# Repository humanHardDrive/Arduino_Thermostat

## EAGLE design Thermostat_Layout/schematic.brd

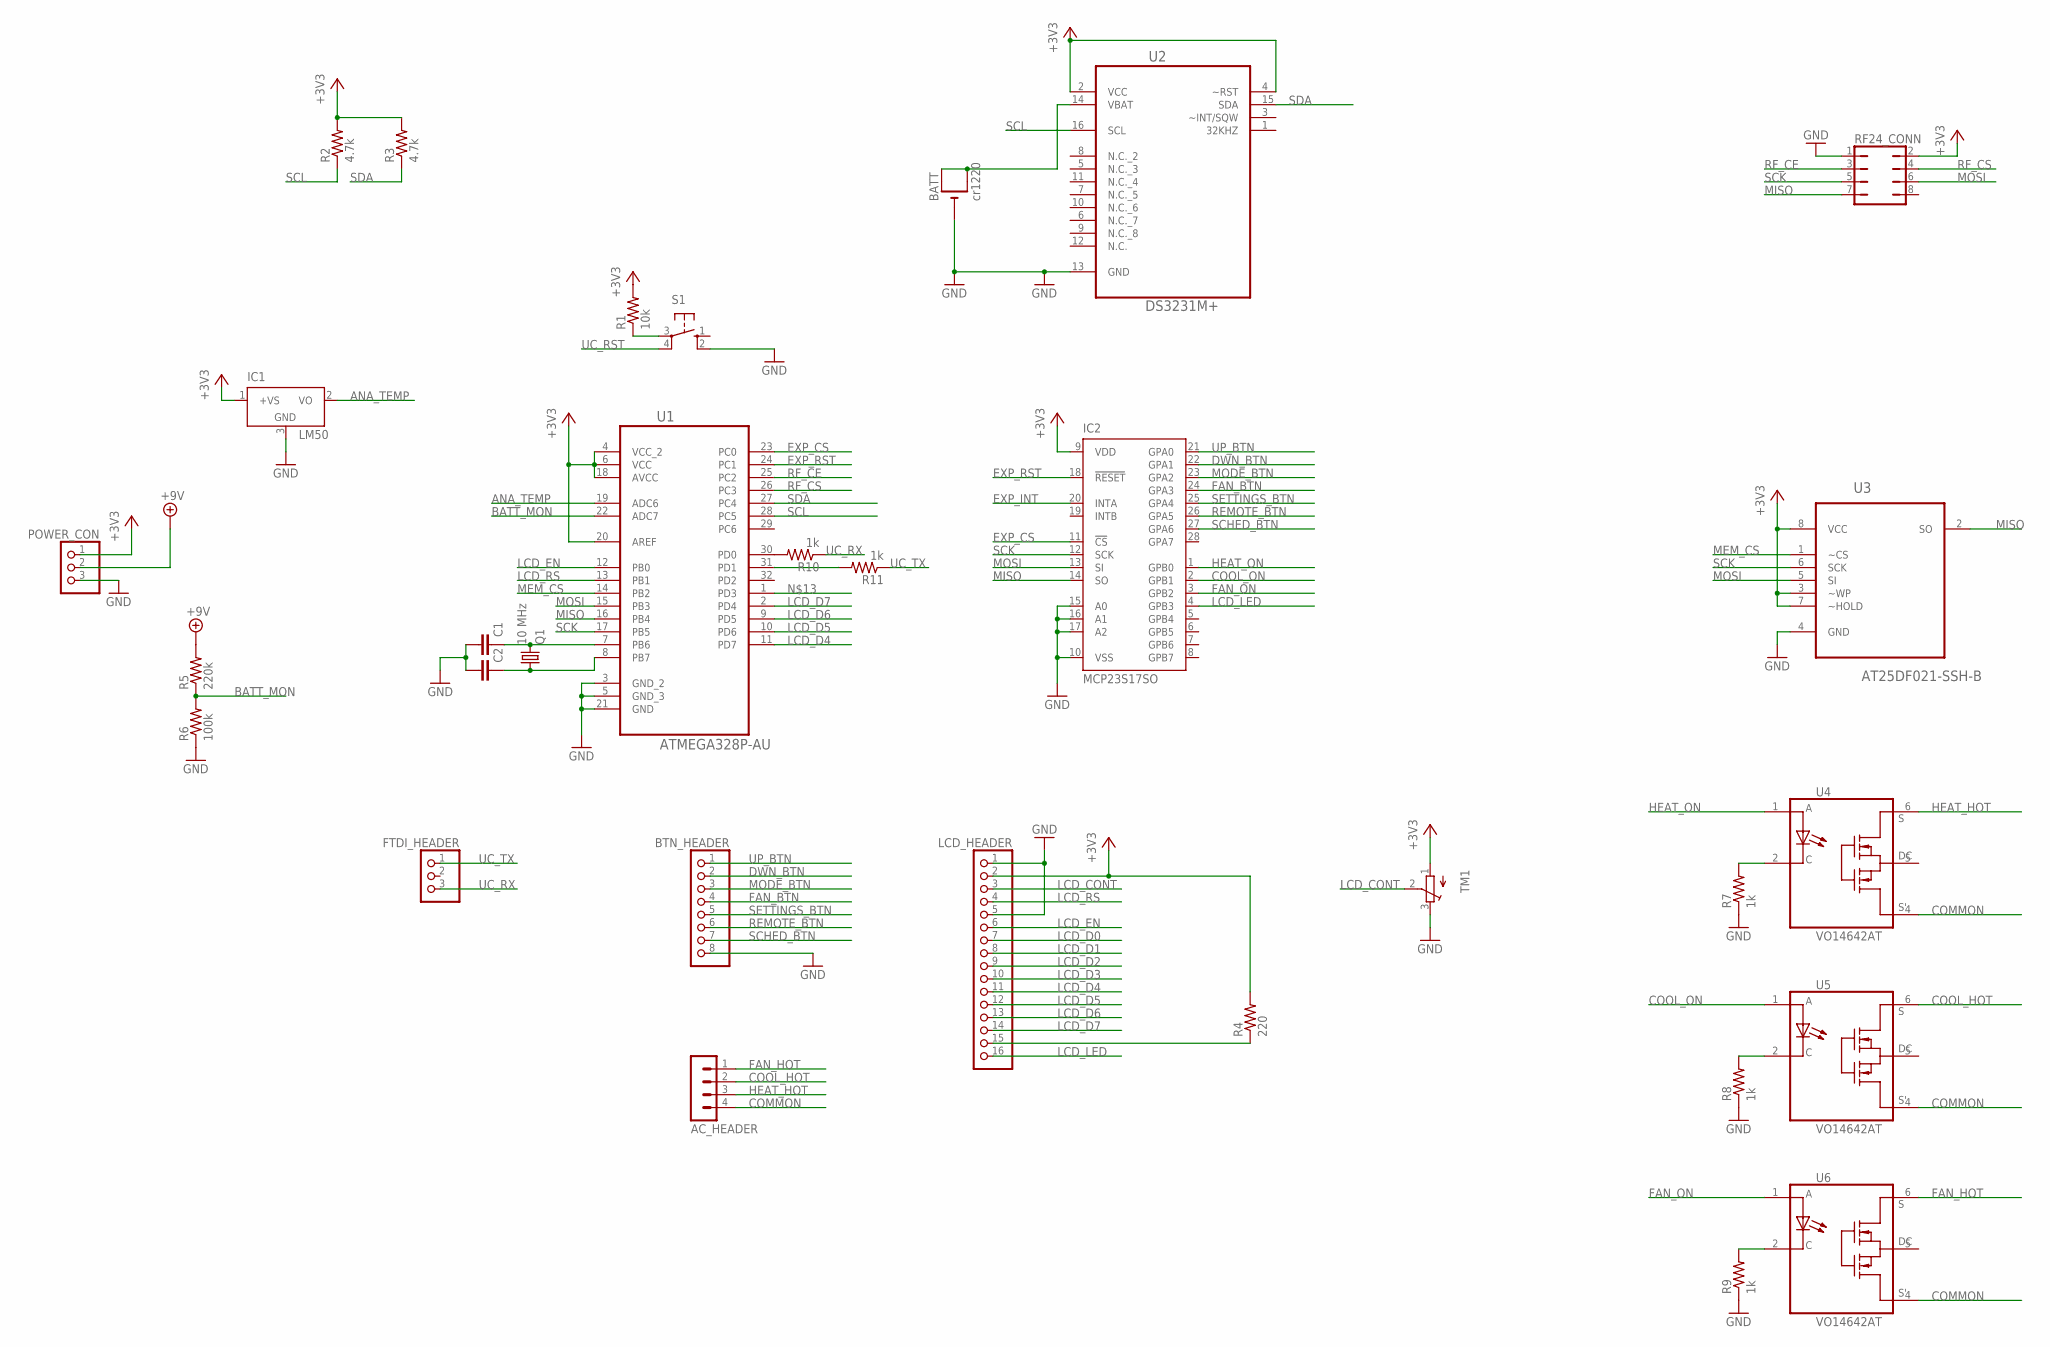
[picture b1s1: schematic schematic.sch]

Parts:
AC_HEADER: MA04-1
BATT: cr1220; CR1220-SMD
BTN_HEADER: PINHD-1X8BIG; 1X08-BIG
C1, C2: C-EUC0402; C0402
FTDI_HEADER: PINHD-1X3; 1X03
IC1: LM50; SOT23
IC2: MCP23S17SO; SO28W
LCD_HEADER: PINHD-1X16; 1X16
POWER_CON: PINHD-1X3; 1X03
Q1: 10 MHz; FC-12M
R1: 10k; R0402
R2, R3: 4.7k; R0402
R4: 220; R0402
R5: 220k; R0402
R6: 100k; R0402
R7, R8, R9, R10, R11: 1k; R0402
RF24_CONN: JP4Q
S1: 10-XX; B3F-10XX
TM1: TRIMPOTTC33X; TC33X
U1: ATMEGA328P-AU; QFP80P900X900X120-32N
U2: DS3231M+; SOIC127P1032X265-16N
U3: AT25DF021-SSH-B; SOIC127P600X175-8N
U4, U5, U6: VO14642AT; DIP762W50P254L730H410Q6

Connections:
+3V3: IC1.1 (+VS), IC2.9 (VDD), LCD_HEADER.2, POWER_CON.1, R1.2, R2.2, R3.2, R4.2, RF24_CONN.2, TM1.1 (A), U1.4 (VCC_2), U1.6 (VCC), U1.18 (AVCC), U1.20 (AREF), U2.2 (VCC), U2.4 (~RST), U3.3 (~WP), U3.7 (~HOLD), U3.8 (VCC)
+9V: POWER_CON.2, R5.2
ANA_TEMP: IC1.2 (VO), U1.19 (ADC6)
BATT_MON: R5.1, R6.2, U1.22 (ADC7)
COMMON: AC_HEADER.4, U4.4 (S'), U5.4 (S'), U6.4 (S')
COOL_HOT: AC_HEADER.2, U5.6 (S)
COOL_ON: IC2.2 (GPB1), U5.1 (A)
DWN_BTN: BTN_HEADER.2, IC2.22 (GPA1)
EXP_CS: IC2.11 (!CS), U1.23 (PC0)
EXP_INT: IC2.20 (INTA)
EXP_RST: IC2.18 (!RESET), U1.24 (PC1)
FAN_BTN: BTN_HEADER.4, IC2.24 (GPA3)
FAN_HOT: AC_HEADER.1, U6.6 (S)
FAN_ON: IC2.3 (GPB2), U6.1 (A)
GND: BATT.-, BTN_HEADER.8, C1.2, C2.2, IC1.3 (GND), IC2.10 (VSS), IC2.15 (A0), IC2.16 (A1), IC2.17 (A2), LCD_HEADER.1, LCD_HEADER.5, POWER_CON.3, R6.1, R7.1, R8.1, R9.1, RF24_CONN.1, S1.2 (S1), TM1.3 (E), U1.3 (GND_2), U1.5 (GND_3), U1.21 (GND), U2.13 (GND), U3.4 (GND)
HEAT_HOT: AC_HEADER.3, U4.6 (S)
HEAT_ON: IC2.1 (GPB0), U4.1 (A)
LCD_CONT: LCD_HEADER.3, TM1.2 (S)
LCD_D0: LCD_HEADER.7
LCD_D1: LCD_HEADER.8
LCD_D2: LCD_HEADER.9
LCD_D3: LCD_HEADER.10
LCD_D4: LCD_HEADER.11, U1.11 (PD7)
LCD_D5: LCD_HEADER.12, U1.10 (PD6)
LCD_D6: LCD_HEADER.13, U1.9 (PD5)
LCD_D7: LCD_HEADER.14, U1.2 (PD4)
LCD_EN: LCD_HEADER.6, U1.12 (PB0)
LCD_LED: IC2.4 (GPB3), LCD_HEADER.16
LCD_RS: LCD_HEADER.4, U1.13 (PB1)
MEM_CS: U1.14 (PB2), U3.1 (~CS)
MISO: IC2.14 (SO), RF24_CONN.7, U1.16 (PB4), U3.2 (SO)
MODE_BTN: BTN_HEADER.3, IC2.23 (GPA2)
MOSI: IC2.13 (SI), RF24_CONN.6, U1.15 (PB3), U3.5 (SI)
unnamed: C1.1, Q1.2, U1.7 (PB6)
unnamed: C2.1, Q1.1, U1.8 (PB7)
unnamed: LCD_HEADER.15, R4.1
unnamed: R1.1, S1.3
unnamed: R7.2, U4.2 (C)
unnamed: R8.2, U5.2 (C)
unnamed: R9.2, U6.2 (C)
unnamed: BATT.+$1 (+), BATT.+$2 (+1), U2.14 (VBAT)
unnamed: R10.2, U1.30 (PD0)
unnamed: R11.2, U1.31 (PD1)
REMOTE_BTN: BTN_HEADER.6, IC2.26 (GPA5)
RF_CE: RF24_CONN.3, U1.25 (PC2)
RF_CS: RF24_CONN.4, U1.26 (PC3)
SCHED_BTN: BTN_HEADER.7, IC2.27 (GPA6)
SCK: IC2.12 (SCK), RF24_CONN.5, U1.17 (PB5), U3.6 (SCK)
SCL: R2.1, U1.28 (PC5), U2.16 (SCL)
SDA: R3.1, U1.27 (PC4), U2.15 (SDA)
SETTINGS_BTN: BTN_HEADER.5, IC2.25 (GPA4)
UC_RST: S1.4 (P1)
UC_RX: FTDI_HEADER.3, R10.1
UC_TX: FTDI_HEADER.1, R11.1
UP_BTN: BTN_HEADER.1, IC2.21 (GPA0)

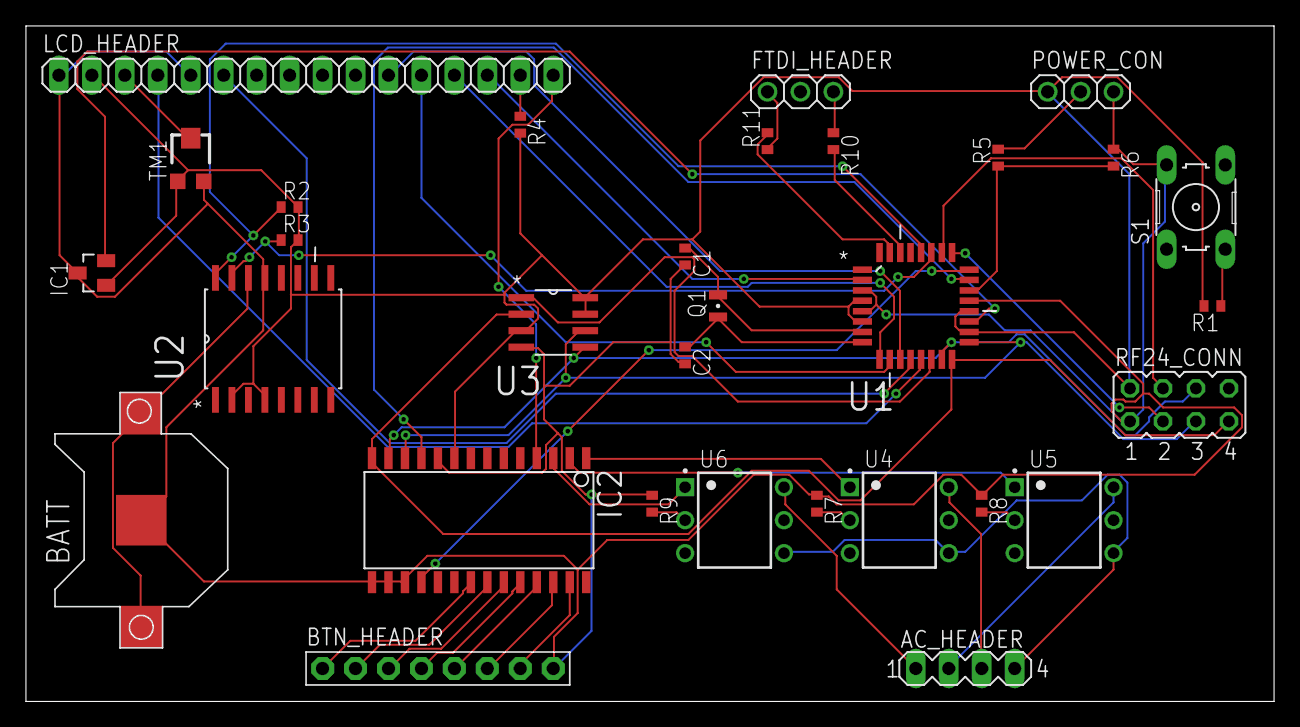
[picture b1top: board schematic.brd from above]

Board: 2 copper layers, 96.2 x 52.1 mm, 31 parts (0 on the bottom side), 49 nets.

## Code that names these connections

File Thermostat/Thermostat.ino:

#include <Wire.h>
#include <DS3231.h>
#include <LiquidCrystal.h>
#include <Sleep_n0m1.h>
#include <Streaming.h>

#include "ThermostatDevice.h"
#include "SensorDevice.h"
#include "ESPInterface.h"

#define APP_NAME    F("REMOTE THERMOSTAT")
#define VERSION_MAJOR   0
#define VERSION_MINOR   0

/*Basic logging macro*/
#define LOG Serial << "\n\r" << millis() << '\t' << __FUNCTION__ << '\t'

//Arduino Pins
#define IO_EXP_RST_PIN  13
#define ESP_RST_PIN     12
#define ESP_EN_PIN      11
#define ESP_ST_PIN      10
#define LCD_RS_PIN      9
#define LCD_EN_PIN      8
#define LCD_D4_PIN      7
#define LCD_D5_PIN      6
#define LCD_D6_PIN      5
#define LCD_D7_PIN      4
#define HEARTBEAT_PIN   3
#define IO_EXP_INT_PIN  2

#define BATT_MON_EN_PIN A0
#define DBG_TX_PIN      A1
#define DBG_RX_PIN      A2
#define I2C_SDA         A4
#define I2C_SCL         A5
#define LOCAL_TEMP_PIN  A6
#define BATT_MON_PIN    A7

struct SaveInfo
{
  APInfo apInfo;
  ServerInfo serverInfo;

  uint16_t checksum;
};

SaveInfo saveInfo;

ESPInterface      espInterface;
SensorDevice      sensorDevice(LOCAL_TEMP_PIN, 1000, 1000);
ThermostatDevice  thermostatDevice(espInterface);

DS3231 Clock;
RTClib RTC;

bool bNeedRealTime = true;
uint32_t nLastTimePoll = 0;

char* sPubAliasList[] =
{
  "CurrentTemp",
  "CurrentMode",
  "" /*The empty string is the end of the array*/
};

char* sSubAliasList[] =
{
  "TargetTemp",
  "TargetMode",
  ""
};

bool waitForESPResponse(uint8_t cmd, void* outBuf, uint8_t outLen, void** inBuf, uint32_t timeout)
{
  bool bMsgReady = false;
  uint32_t nStartTime;
  uint8_t inCmd;

  espInterface.sendCommand(cmd, outBuf, outLen);
  delay(1);
  nStartTime = millis();

  while ((millis() - nStartTime) < timeout && !bMsgReady)
  {
    if (Serial.available())
    {
      espInterface.background(Serial.read());
      bMsgReady = espInterface.messageReady(&inCmd, inBuf);

      /*Continue processing messages while waiting for the response*/
      if (bMsgReady)
      {
        if (inCmd != cmd)
        {
          LOG << F("Unexpected response for cmd type ") << inCmd;
          bMsgReady = false;
        }
        /*Reset timer*/
        nStartTime = millis();
      }
    }
  }

  if (!bMsgReady)
  {
    LOG << F("No message returned");
    return false;
  }

  return true;
}

bool InitESPInterface()
{
  uint8_t *buf;

  LOG << F("Resetting ESP interface");
  digitalWrite(ESP_RST_PIN, LOW);
  delay(1);
  digitalWrite(ESP_RST_PIN, HIGH);

  /*Wait at most 10 seconds for the interface to show ready status*/
  uint32_t nStatusStartTime = millis();
  while ((millis() - nStatusStartTime) < 10000 &&
         digitalRead(ESP_ST_PIN))
  {
  }

  if (digitalRead(ESP_ST_PIN))
  {
    LOG << F("Interface didn't show ready status in time");
    return false;
  }

  return true;
}

void RecoverInfo()
{
  memset(&saveInfo, 0, sizeof(SaveInfo));

  thermostatDevice.setOffset(sizeof(SaveInfo));
  thermostatDevice.recover();
}

bool InitIOExpander()
{
  return false;
}

bool InitRTC()
{
  DateTime then = RTC.now();
  delay(1500);

  if (RTC.now().unixtime() == then.unixtime())
  {
    LOG << F("Failed to see clock change");
    return false;
  }

  LOG << F("Date ") << then.day() << '/' << then.month() << '/' << then.year();
  LOG << F("Time ") << then.hour() << ':' << then.minute();

  return true;
}

void setup()
{
  /*Setup serial*/
  Serial.begin(57600);
  Wire.begin();

  /*Setup pin directions*/
  pinMode(ESP_RST_PIN, OUTPUT);
  pinMode(ESP_ST_PIN, INPUT_PULLUP);

  /*Initialize components*/
  if (!InitESPInterface())
  {
    LOG << F("Failed to init ESP interface");
    while (1);
  }

  if (!InitRTC())
  {
    LOG << F("Failed to init RTC");
    while (1);
  }
}

void loop()
{
  if (bNeedRealTime && (millis() - nLastTimePoll) > 30000)
  {
    uint32_t* pCurrentTime;
    if (waitForESPResponse(TIME, NULL, 0, &pCurrentTime, 10))
    {
      if (*pCurrentTime)
      {
        LOG << F("Got current time");
        bNeedRealTime = false;
      }
      else
        LOG << F("ESP isn't connected to internet. Can't get time");
    }

    nLastTimePoll = millis();
    if (bNeedRealTime)
      LOG << F("Couldn't get time from ESP interface");
  }
}

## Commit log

2019-04-10 Remove project files. Add library
2019-04-10 Add project for thermostat to help build library
2019-04-10 Add temperature sensor project. Other changes.
2019-04-10 Flush out some methods to send messages
2019-04-13 Add LCD for menus and more interfaces.
2019-04-13 Put interface buttons on the IO expander
2019-04-14 Add modes for fan control and heat
2019-04-18 Add RTC library
    Use the RTC to set the target temperature based on a timed rule set.
2019-04-24 Add method to calculate day of week
2019-04-28 Add RF24 radio to thermostat
2019-04-29 Start setting up the remote temperature sensor.
2019-04-30 Setup more of the thermostat's communication
    Handle entering and exiting discovery mode. Added some debug serial commands to interface without buttons.
2019-04-30 Fix timeout calculation
2019-04-30 Add funciton to build packets
2019-05-07 First successful recieve and trasmit
    Need to get the discovery pipe working properly and parse the message on the sensor side.
2019-05-07 Modify discovery pipe
2019-05-09 Setup message handling and basic discovery
2019-05-10 Set first half of initialization
2019-05-10 Create comm base to recyle code
2019-05-11 Remove old code. Verify new functionality.
    The discovery message now only acts as a discovery, not discovery and pair. The remote device returns a name to be identified.
2019-05-11 Handle device discovery.
    List out all of the discovered devices
2019-05-11 Setup first half of pairing
    Memory limitations are now something to consider on the base station
2019-05-11 Use the network ID as the reading/writing pipe
2019-05-19 Setup messages on the sensor to send temperature reading
2019-05-19 Start setting up handlers for temperature messages
    Started adding hooks to retry messages.
2019-05-19 Move message retry vars to base class
2019-05-19 Try to get some memory back
2019-05-19 Move the vars back
2019-05-19 Handle messages on the temperature sensor
2019-05-19 Handle invalid dyanmic payloads
2019-05-20 Simplify reads for the base station. Fix memcpy over memset
2019-05-20 Fix base station buffer size to read full discovery message
2019-05-20 Retry during remote pairing
    Verify the source and message type from the message to finish the pairing process.
2019-05-20 Use the pairing message to update the remote radio
2019-05-21 Change command handler to virtual
2019-05-21 Add method to add paired device to saved list
2019-05-22 Add paired device to saved data list
2019-05-22 Only handle messages from paired devices
2019-05-23 Setup the menu to use the LCD
2019-05-23 Create some strings for the display
2019-05-23 Add function to rename paired devices
2019-05-24 Create boot output with LCD
2019-05-24 Change to use defines over string table
2019-05-24 Initialize temperature rules structure before overwritten by flash
2019-05-24 Add check for IO expander on startup
    Simplify the io expander class for now.
2019-05-25 Add button debounce to IO expander
2019-05-25 Move boot into separate functions
2019-05-25 Print day and time on LCD
2019-05-25 Create local temperature sensor for the base station
    Use a thermistor and do math
2019-05-26 Setup hysteresis for switching heat/cool on and off
2019-05-27 Switch to a different memory chip
2019-05-27 Change to a bigger LCD
2019-05-28 Create control methods for FRAM
2019-05-28 Pass FRAM to thermostat class.
    Create a memory offset parameter to be used in all reads and writes.
2019-05-28 Use memory device to finish save/load functions
2019-05-28 Add sanity checks to prevent null pointer access
2019-05-28 Create startup test for FRAM
2019-05-30 Update storage test
2019-05-31 Recover settings from NV memory
    Move the calls to reset and restore to the child class
2019-05-31 Share memory library with temperature sensor
2019-05-31 Update sensor with recover/reset/save functions
2019-06-01 Start laying out the thermostat schematic
2019-06-01 Reorder pins to get IO expander interrupt
2019-06-01 Sleep and wake to save battery
2019-06-02 Updates to the menu
2019-06-02 Scroll through menu
2019-06-02 Add more main menu controls
2019-06-03 Scroll through paired devices on menu
2019-06-03 Store remote temperatures in array
2019-06-03 Drop support for celsius
2019-06-03 Add message for remote to request being used as sensor
2019-06-03 Handle new message request on base station
    Clean up debug print statments.
2019-06-04 Be able to enter and exit settings menu
    Need to clean up these menus at a later point
2019-06-05 Sleep the sensor to perserve power
2019-06-05 Stay awake while pairing
    Update the library to have getters for the discovery state.
2019-06-05 Add LED control to display sensor state
2019-06-06 Take periodic temperature readings. Rename a few things
2019-06-06 Softly blink LED while pairing
2019-06-06 Heartbeat while not pairing
2019-06-07 Try new menu control
    Probably not too menu friendly, but makes cleaner code.
2019-06-07 Move menu itmes into flash. Rename headers.
2019-06-07 Remove old menu functions
2019-06-07 More menu changes
2019-06-07 Update temperature reading on the base station
2019-06-08 Do away with the complex menu idea
2019-06-09 Update the schedule and mode lines on the LCD
    Only update the LCD when needed.
2019-06-09 Update the time string on the LCD
2019-06-09 Reorder some menu elements. Add the sensor menu element
2019-06-09 Create scrollable setting menu
2019-06-09 Limit the settings drawing to whatever's changed
2019-06-09 Can't test discovery without the radio attached
2019-06-10 Move to using the raw DS3231 library calls. Finish the day/time setting
2019-06-27 Update schematic
2019-06-27 More schematic updates
2019-06-28 More layout changes
2019-07-05 Add a second IO expander to handle LCD
2019-07-21 Clean up schematic and board
2019-08-07 Switch to KiCad for layout. Finished the thermostat layout.
2019-08-08 Update remote sensor layout
2019-08-10 Update processor pin definitions
2019-08-11 Add new messages for the remote sensor
2019-08-11 Fix sleep state
2019-08-11 Fix analog temperature reading. Add button schematic.
2019-08-12 Update button board PCB
2019-08-13 Attempted menu class
2019-08-17 Menu stuff
2019-10-05 Remove unused libraries
2019-10-05 Add ESP8266 project
2019-10-05 Remove NRF24 from schematic
2019-10-05 Remove nrf24 code from sensor
2019-10-06 Remove RF24 and base station code from thermostat
2019-10-10 Layout changes
2019-10-10 Add saved info structure to store network info
2019-10-10 Complete radio schematic
2019-10-10 Swap out the MCP23s17 for the MCP23017
    Removes the need for the SPI bus
2019-10-11 FInalize schematic for thermostat
2019-10-12 Add serial interface and some state handlers
2019-10-12 Call command handler upon complete message
2019-10-12 Reset parse state after a certain amount of time
2019-10-12 Comments
2019-10-13 Add debug serial. Add command handler stuff.
2019-10-13 Make commands case insensitive
2019-10-31 Schematic and PCB layout for thermostat
2019-10-31 Button board layout with mini joystick
2019-10-31 Add output
2019-10-31 Button PCB update
2019-11-03 Folder rename
2019-11-08 Move interface to separate repository
2019-11-24 Remove uneeded headers
2019-11-24 Cleanup
    Need to re-write the IO expander to support I2C
2019-11-24 Put back the MCP library. Add link to Msgs.h for MQTT interface
2019-11-24 Add interface for ESP
2019-12-04 Move some components around
2019-12-15 Implement serial methods for ESP interface
2019-12-15 Check for ESP communication on startup
2019-12-15 Message ready function returns current message buffer
2019-12-15 Tear down. Start over.
2019-12-15 Update pin definitions
2019-12-22 Query ESP interface for version to establish connection
2019-12-22 Create function to send and wait for ESP response. Add init of RTC
2019-12-22 Poll for time on startup
2019-12-22 Limit error messages for initialized ESP interface
2019-12-23 Change ESP interface to have a command queue. Process messages while waiting for command response.
2020-04-11 Cleanup old thermostat code
2020-04-11 Send pub/sub alias on startup
2020-04-11 Start the network helper before connecting to an AP
2020-04-19 Add memory interface classes
2020-04-19 Create thermostat device
2020-04-19 Setup thermostat device
2020-04-20 Flesh out more of the thermostat device
2020-04-22 Setup remote sensor class
2020-04-22 Setup temperature sampling
2020-04-22 Remove software serial. Change STX to non-ASCII set
2020-05-16 Remove notification model
2020-05-16 Remove old code
2020-05-16 Add files
2020-05-16 Setup pins and basic sleep
2020-05-16 Setup reset latch
2020-05-17 Update sensor
2020-05-18 Reorganize folders. New remote layout.
2020-05-21 Add lipo support
2020-05-21 Finish schematic
2020-05-23 More power control. Add some mounting holes.
2020-05-23 Generate PCB
2020-05-23 Update IO map
2020-05-23 Finalize PCB
2020-05-23 Autotrace
2020-05-24 Copper pour
2020-05-24 Fix resistor on wrong side
2020-05-24 Add schematic PDF
2020-05-24 Update IO map. Blink heartbeat while awake.
2020-05-24 Update LED status
2020-05-24 Monitor button state changes
    Refresh the wake time every time a button is hit.
2020-05-24 Add MQTT components
2020-05-24 Cleanup thermostat layout
2020-05-25 Add saved info structure
2020-05-27 New schematics
2020-05-27 Setup EEPROM
2020-05-29 Create running state functions
2020-05-29 Setup state function map
2020-05-30 Add method to build device name
2020-05-30 Recover saved info
2020-05-30 Add MQTT paths to saved info structure
2020-05-30 Verify info before trying to connect to MQTT server
2020-05-30 Setup subscriptions and publications
2020-05-30 Fill out sleep states
2020-06-12 Change some component values
2020-06-12 Fix charger and battery status
2020-06-13 Remove power control for temperature sensor
2020-06-16 Add second regulator for USB
2020-06-17 Move circuits on different sheets
2020-06-17 Update schematic sheet
2020-06-21 Add an IO expander
2020-06-21 Assign footprints
2020-06-25 Add FTDI USB to serial
2020-06-25 Update sensor schematic
2020-06-27 Add footprints and component values
2020-06-28 Edit layout
2020-07-01 New PCB layout
2020-07-01 Update schematic PDF
2020-07-04 Change pin definitions
2020-07-04 Setup new IO map
2020-07-05 Debounce inputs. Add handlers
2020-08-08 Change the USB switching regulator for an LDO
2020-08-09 Update PCB layout
2020-08-09 Generate routing
2020-08-10 Update outputs
2020-08-13 Remove pour from keep out zone under antenna
2020-08-29 Switch to X macros
    Debug the board. Issues with the sleep latch
2020-09-07 Change what pins are used for i2c
2020-09-07 Diode protect usb voltage
2020-09-19 Change how power is switched between battery and USB
2020-09-20 Change out nav switch for tactile
2020-09-26 Another layout
2020-09-29 Layout
2021-01-25 Create LICENSE
